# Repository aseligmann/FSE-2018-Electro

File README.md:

# FSE-2018-Electro
Repository for all software, schematics and designs made by the Electrical Department of Vermillion Racing for the 2018 season..

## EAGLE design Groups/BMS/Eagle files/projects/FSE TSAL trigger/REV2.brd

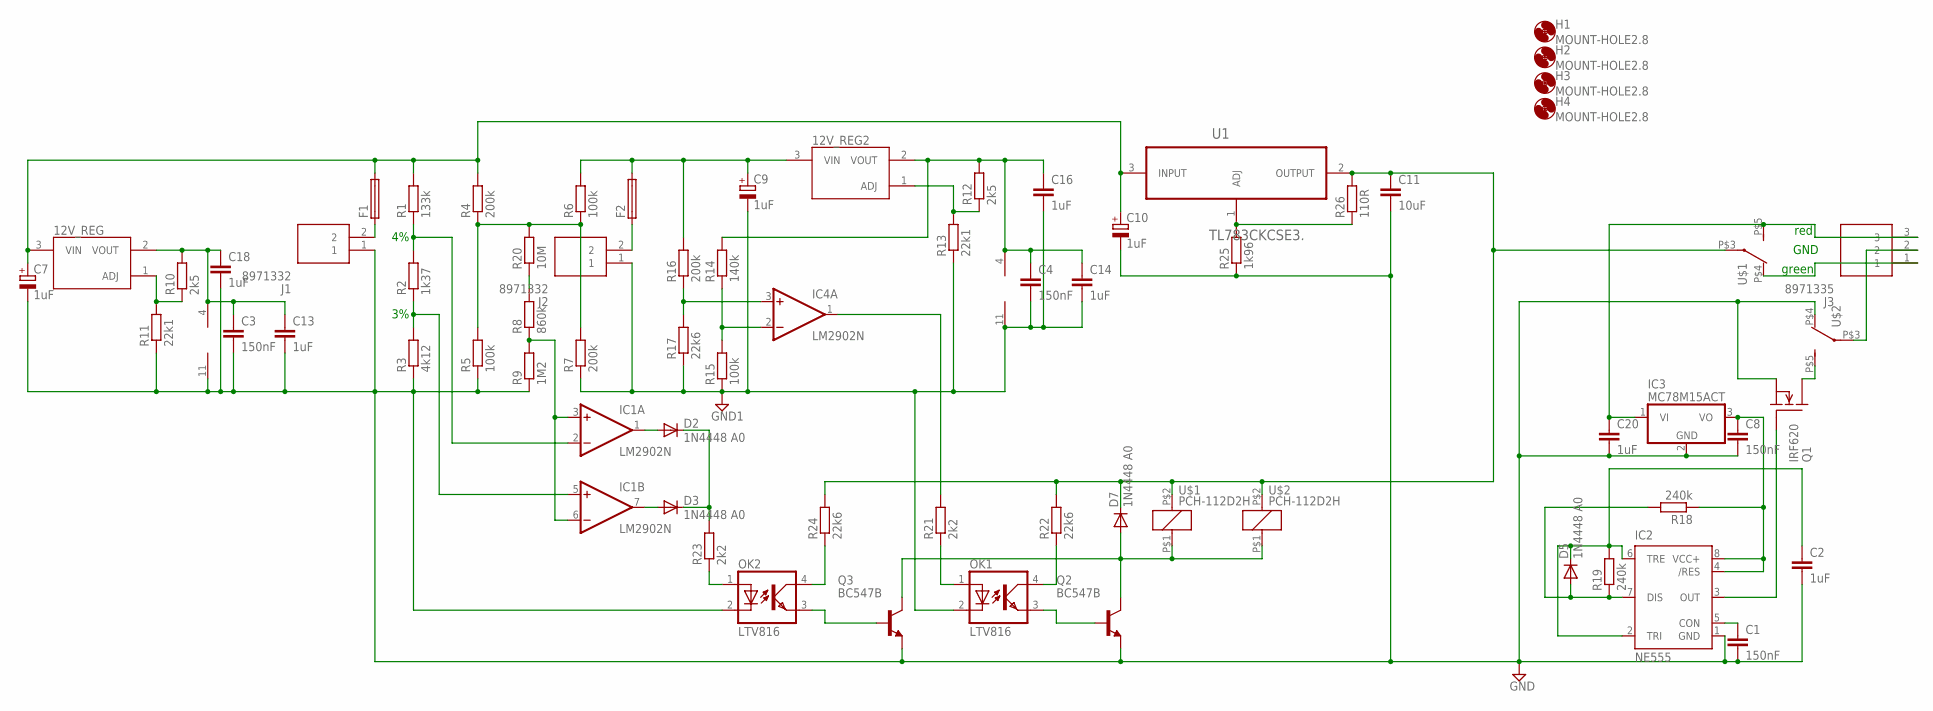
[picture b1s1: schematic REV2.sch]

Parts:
12V_REG, 12V_REG2: LR8LR8; TO92-LINE
C1, C3, C4, C8: 150nF; C050-024X044
C2, C13, C14, C16, C18, C20: 1uF; C025-030X050
C7, C9, C10: 1uF; E3,5-8
C11: 10uF; C050-075X075
D2, D3, D5, D7: 1N4448 A0; DO35-10
F1, F2: GSH15
H1, H2, H3, H4: MOUNT-HOLE2.8; 2,8
IC1, IC4: LM2902N; DIL14
IC2: NE555; DIL-08
IC3: MC78M15ACT; TO220V
J1, J2: 8971332; SHDR2W90P0X350_1X2_700X700X850
J3: 8971335; SHDR3W90P0X350_1X3_1050X700X85
OK1, OK2: LTV816; DIL04
Q1: IRF620; TO220
Q2, Q3: BC547B; TO92
R1: 133k; 0207/10
R2: 1k37; 0207/10
R3: 4k12; 0207/10
R4, R7, R16: 200k; 0207/10
R5, R6, R15: 100k; 0207/10
R8: 860k; 0207/10
R9: 1M2; 0207/10
R10, R12: 2k5; 0207/10
R11, R13: 22k1; 0207/10
R14: 140k; 0207/10
R17, R22, R24: 22k6; 0207/10
R18, R19: 240k; 0207/10
R20: 10M; 0207/10
R21, R23: 2k2; 0207/10
R25: 1k96; 0309/10
R26: 110R; 0309/10
U1: TL783CKCSE3.; TO254P457X1016X2222-3P
U$1, U$2: PCH-112D2H

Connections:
GND: C1.2, C2.2, C3.2, C7.-, C8.2, C10.-, C11.2, C13.2, C18.2, C20.2, IC1.11 (V-), IC2.1 (GND), IC3.2 (GND), J1.1, OK2.2 (C), Q1.3 (S), Q2.1 (E), Q3.1 (E), R3.1, R5.1, R9.1, R11.1, R25.1, U$2.P$4 (O)
GND1: C4.2, C9.-, C14.2, C16.2, IC4.11 (V-), J2.1, OK1.2 (C), R7.1, R13.1, R15.1, R17.1
unnamed: 12V_REG.3 (VIN), C7.+, C10.+, F1.2, R1.2, R4.2, U1.3 (INPUT)
unnamed: IC1.2 (-IN), R1.1, R2.2
unnamed: IC1.5 (+IN), R2.1, R3.2
unnamed: C11.1, D7.C, R22.2, R24.2, R26.2, U1.2 (OUTPUT), U$1.P$2 (1), U$1.P$3, U$2.P$2 (1)
unnamed: 12V_REG2.3 (VIN), C9.+, F2.2, R6.2, R16.2
unnamed: IC2.3 (OUT), Q1.1 (G)
unnamed: F1.1, J1.2
unnamed: IC4.1 (OUT), R21.2
unnamed: 12V_REG.2 (VOUT), C3.1, C13.1, C18.1, IC1.4 (V+), R10.2
unnamed: 12V_REG.1 (ADJ), R10.1, R11.2
unnamed: D2.A, IC1.1 (OUT)
unnamed: D3.A, IC1.7 (OUT)
unnamed: D2.C, D3.C, R23.2
unnamed: F2.1, J2.2
unnamed: C1.1, IC2.5 (CON)
unnamed: D5.A, IC2.7 (DIS), R18.2, R19.1
unnamed: C20.1, IC3.1 (VI), J3.3, U$1.P$5 (S)
unnamed: C2.1, D5.C, IC2.2 (TRI), IC2.6 (TRE), R19.2
unnamed: C8.1, IC2.4 (/RES), IC2.8 (VCC+), IC3.3 (VO), R18.1
unnamed: IC4.3 (+IN), R16.1, R17.2
unnamed: J3.1, U$1.P$4 (O)
unnamed: 12V_REG2.2 (VOUT), C4.1, C14.1, C16.1, IC4.4 (V+), R12.2, R14.2
unnamed: Q1.2 (D), U$2.P$5 (S)
unnamed: IC4.2 (-IN), R14.1, R15.2
unnamed: 12V_REG2.1 (ADJ), R12.1, R13.2
unnamed: R4.1, R5.2, R6.1, R7.2, R20.2
unnamed: IC1.3 (+IN), IC1.6 (-IN), R8.1, R9.2
unnamed: R8.2, R20.1
unnamed: R25.2, R26.1, U1.1 (ADJ)
unnamed: OK2.1 (A), R23.1
unnamed: OK2.4 (COL), R24.1
unnamed: J3.2, U$2.P$3
unnamed: D7.A, Q2.3 (C), Q3.3 (C), U$1.P$1 (2), U$2.P$1 (2)
unnamed: OK2.3 (EMIT), Q3.2 (B)
unnamed: OK1.1 (A), R21.1
unnamed: OK1.4 (COL), R22.1
unnamed: OK1.3 (EMIT), Q2.2 (B)

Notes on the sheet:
green
red
GND

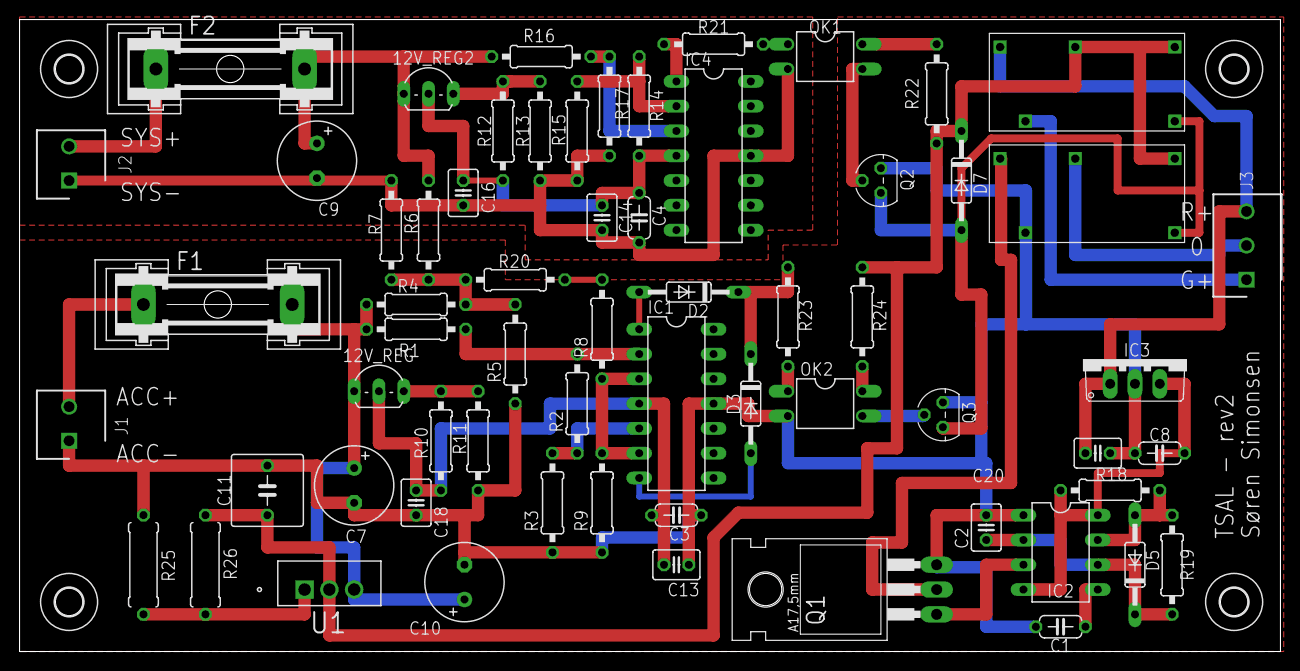
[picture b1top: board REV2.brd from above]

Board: 2 copper layers, 129.2 x 64.8 mm, 67 parts (0 on the bottom side), 39 nets.

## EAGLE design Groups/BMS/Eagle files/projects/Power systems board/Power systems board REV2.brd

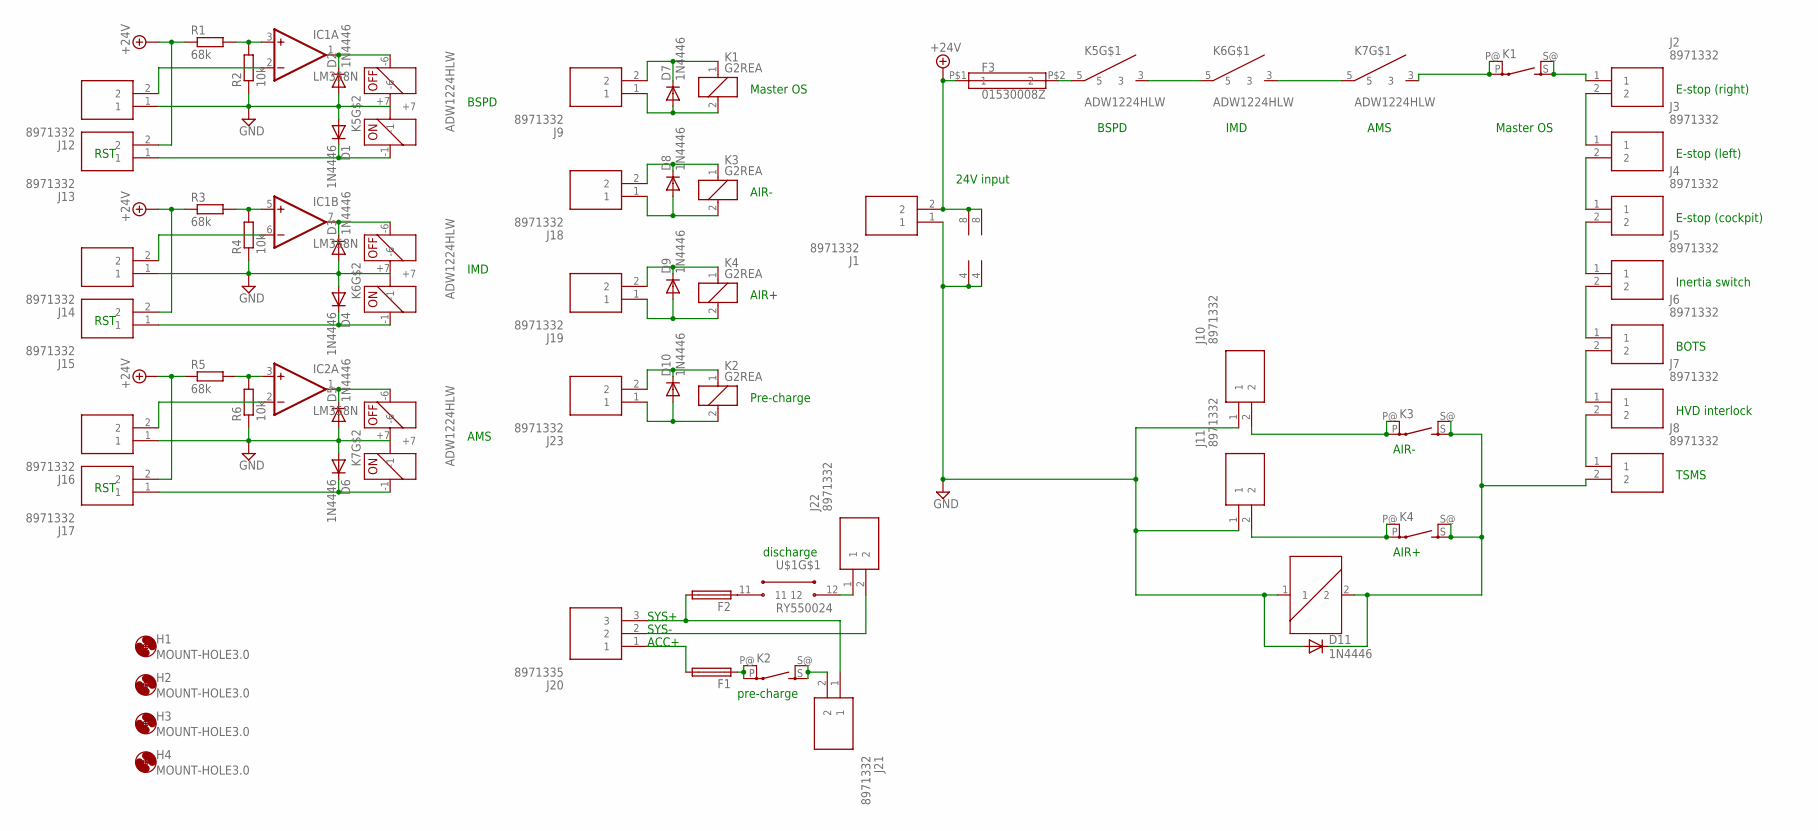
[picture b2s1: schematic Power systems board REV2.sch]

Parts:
D1, D2, D3, D4, D5, D6, D7, D8, D9, D10, D11: 1N4446; DO35-10
F1, F2: GSH15
F3: 01530008Z
H1, H2, H3, H4: MOUNT-HOLE3.0; 3,0
IC1, IC2: LM358N; DIL08
J1, J2, J3, J4, J5, J6, J7, J8, J9, J10, J11, J12, J13, J14, J15, J16, J17, J18, J19, J21, J22, J23: 8971332; SHDR2W90P0X350_1X2_700X700X850
J20: 8971335; SHDR3W90P0X350_1X3_1050X700X85
K1, K2, K3, K4: G2REA
K5, K6, K7: ADW1224HLW
R1, R3, R5: 68k; 0204/7
R2, R4, R6: 10k; 0204/7
U$1: RY550024

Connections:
+24V: F3.P$1 (1), IC1.8 (V+), IC2.8 (V+), J1.2, J13.2, J15.2, J17.2, R1.1, R3.1, R5.1
GND: D1.A, D2.A, D3.A, D4.A, D5.A, D6.A, D11.A, IC1.4 (V-), IC2.4 (V-), J1.1, J10.1, J11.1, J12.1, J14.1, J16.1, K5.+7, K6.+7, K7.+7, R2.1, R4.1, R6.1, U$1.1
unnamed: IC1.3 (+IN), R1.2, R2.2
unnamed: K5.3, K6.5
unnamed: K6.3, K7.5
unnamed: K1.P, K1.P@, K7.3
unnamed: J2.1, K1.S, K1.S@ (S)
unnamed: J2.2, J3.1
unnamed: J3.2, J4.1
unnamed: J4.2, J5.1
unnamed: J5.2, J6.1
unnamed: J6.2, J7.1
unnamed: J7.2, J8.1
unnamed: D11.C, J8.2, K3.S, K3.S@ (S), K4.S, K4.S@ (S), U$1.2
unnamed: J10.2, K3.P, K3.P@
unnamed: J11.2, K4.P, K4.P@
unnamed: F1.1, K2.P, K2.P@
unnamed: D2.C, IC1.1 (OUT), K5.-6
unnamed: IC1.2 (-IN), J12.2
unnamed: D1.C, J13.1, K5.-1
unnamed: IC1.5 (+IN), R3.2, R4.2
unnamed: IC1.6 (-IN), J14.2
unnamed: D5.C, IC2.1 (OUT), K7.-6
unnamed: D4.C, J15.1, K6.-1
unnamed: D3.C, IC1.7 (OUT), K6.-6
unnamed: D7.C, J9.2, K1.1
unnamed: IC2.2 (-IN), J16.2
unnamed: IC2.3 (+IN), R5.2, R6.2
unnamed: D7.A, J9.1, K1.2
unnamed: D6.C, J17.1, K7.-1
unnamed: D8.C, J18.2, K3.1
unnamed: D8.A, J18.1, K3.2
unnamed: D9.C, J19.2, K4.1
unnamed: D9.A, J19.1, K4.2
unnamed: F1.2, J20.1
unnamed: F2.2, J20.3, J21.1
unnamed: J21.2, K2.S, K2.S@ (S)
unnamed: J20.2, J22.2
unnamed: D10.C, J23.2, K2.1
unnamed: D10.A, J23.1, K2.2
unnamed: F3.P$2 (2), K5.5
unnamed: F2.1, U$1.11
unnamed: J22.1, U$1.12

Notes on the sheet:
24V input
BSPD
IMD
AMS
Master OS
E-stop (right)
E-stop (left)
E-stop (cockpit)
Inertia switch
BOTS
HVD interlock
TSMS
Pre-charge
AIR-
AIR+
RST
SYS+
SYS-
ACC+
pre-charge
discharge

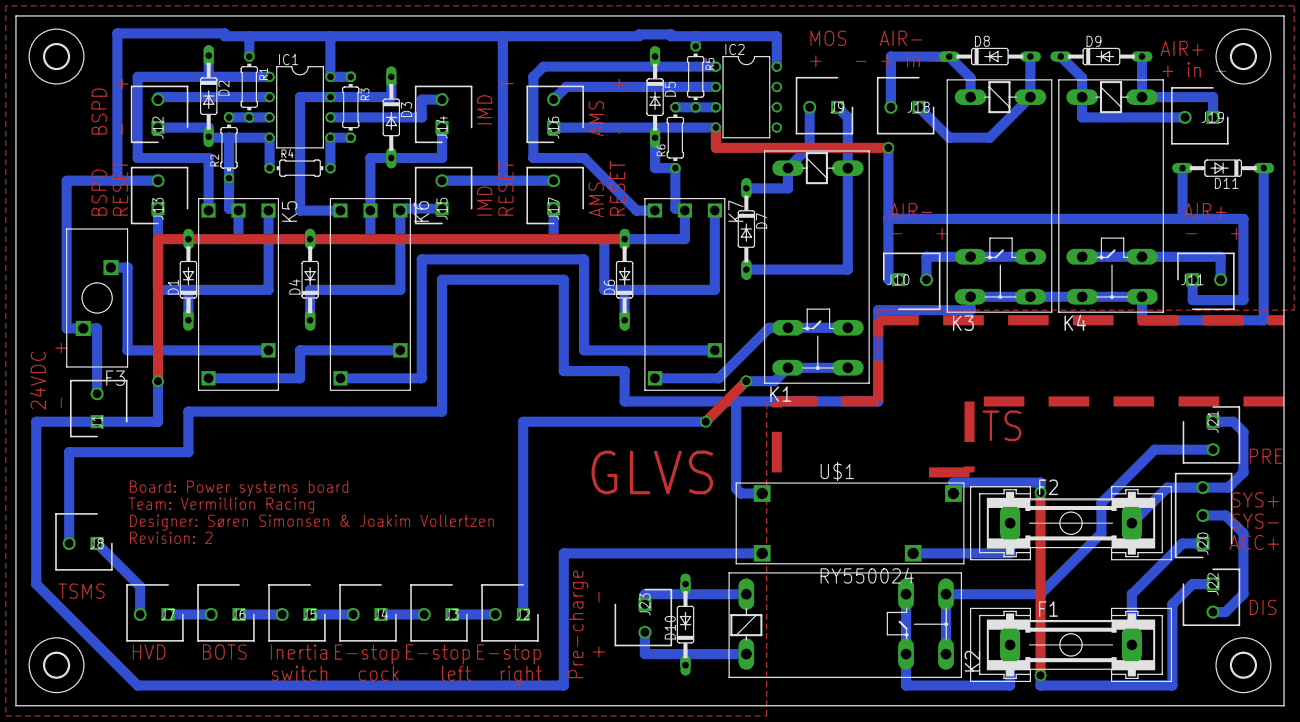
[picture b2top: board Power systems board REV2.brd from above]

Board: 2 copper layers, 158.8 x 86.4 mm, 57 parts (0 on the bottom side), 43 nets.

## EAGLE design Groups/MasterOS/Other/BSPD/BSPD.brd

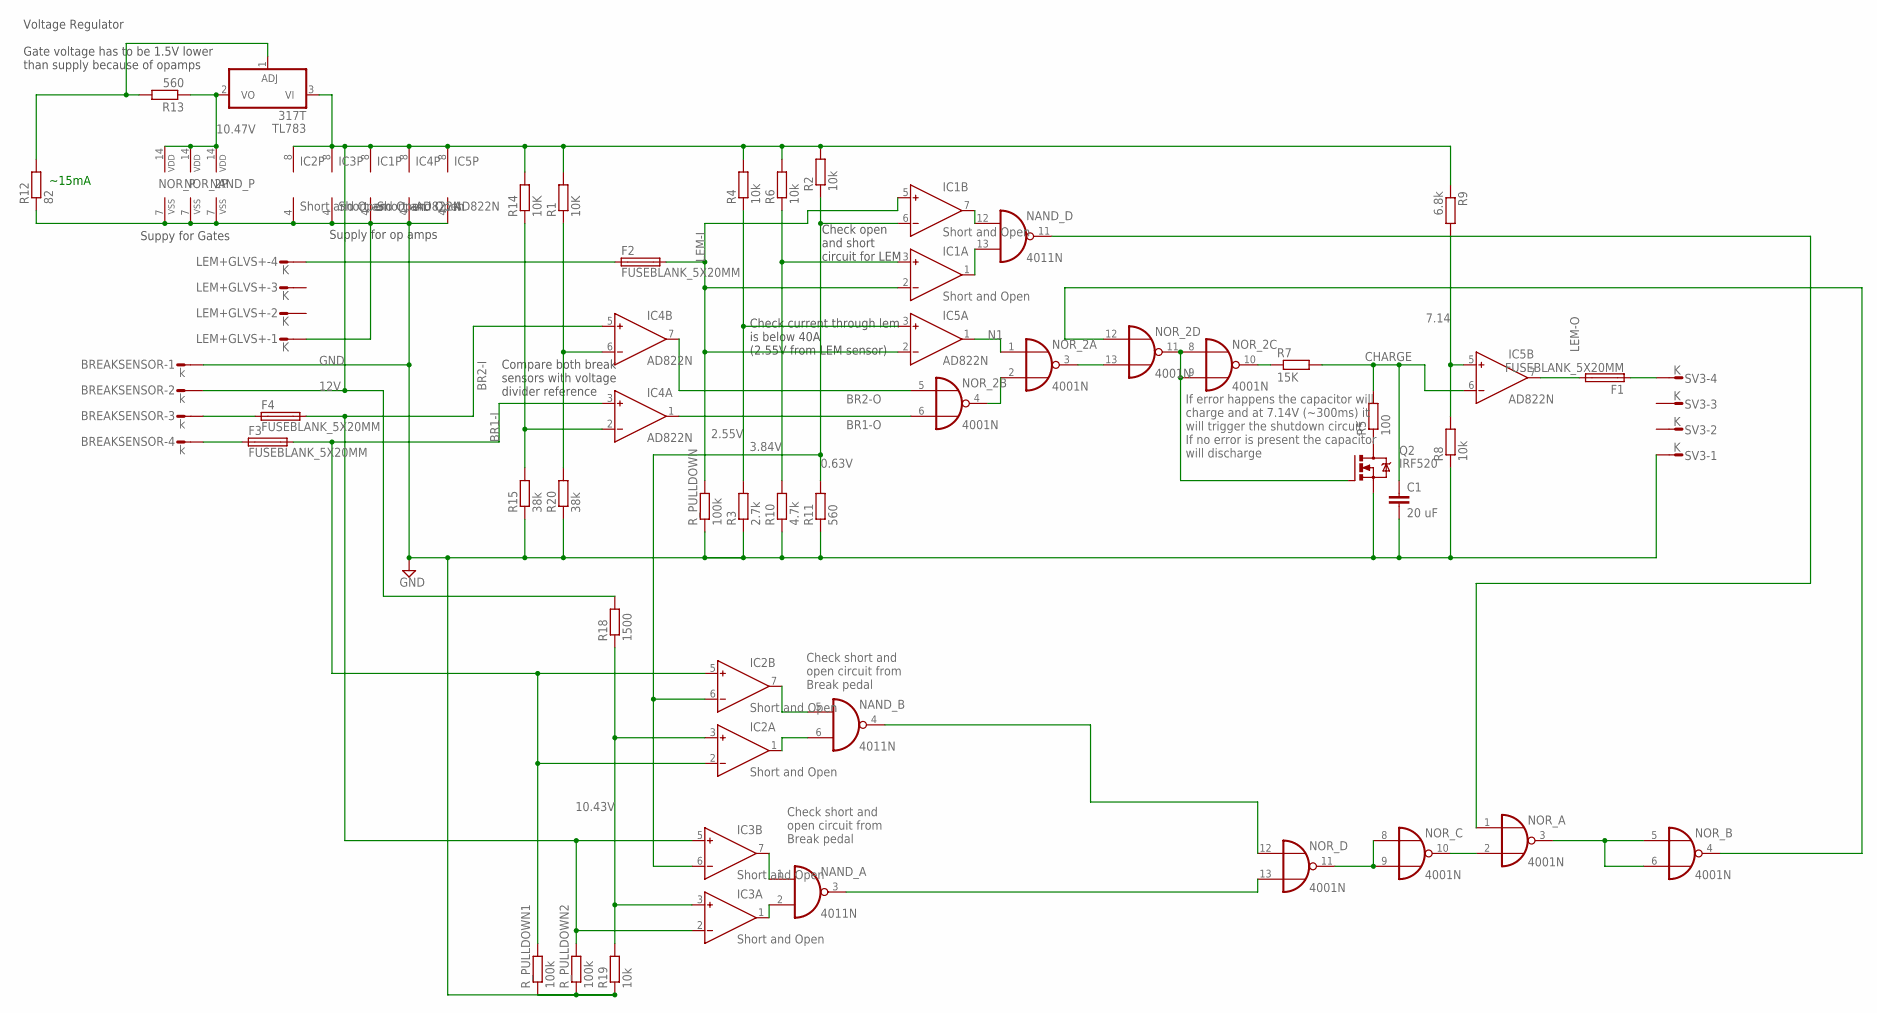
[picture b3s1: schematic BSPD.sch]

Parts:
BREAKSENSOR: k; L04P
C1: 20 uF; C2.5-5
F1, F2, F3, F4: FUSEBLANK_5X20MM; FUSE_HOLDER_5X20MM
IC1, IC2, IC3: Short and Open; DIL08
IC4, IC5: AD822N; DIL08
LEM+GLVS+: K; L04P
NAND_: 4011N; DIL14
NOR_, NOR_2: 4001N; DIL14
Q2: IRF520; TO220BV
R1, R14: 10K; 0204/7
R2, R4, R6, R8: 10k; 0204/7
R3: 2.7k; 0204/7
R5: 100; 0207/10
R7: 15K; 0207/10
R9: 6.8k; 0204/7
R10: 4.7k; 0204/7
R11, R13: 560; 0204/7
R12: 82; 0204/7
R15, R20: 38k; 0207/10
R18: 1500; 0207/10
R19: 10k; 0207/10
R_PULLDOWN, R_PULLDOWN1, R_PULLDOWN2: 100k; 0204/7
SV3: K; L04P
TL783: 317T; TO220H

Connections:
0.63V: IC1.6 (IN-), IC2.6 (IN-), IC3.6 (IN-), R2.1, R11.2
2.55V: IC5.3 (IN+), R3.2, R4.1
3.84V: IC1.3 (IN+), R6.1, R10.2
7.14: IC5.5 (IN+), R8.2, R9.2
10.43V: IC2.3 (IN+), IC3.3 (IN+), R18.1, R19.2
10.47V: NAND_.14 (VDD), NOR_.14 (VDD), NOR_2.14 (VDD), R13.1, TL783.2 (VO)
12V: BREAKSENSOR.2, IC1.8 (V+), IC2.8 (V+), IC3.8 (V+), IC4.8 (V+), IC5.8 (V+), R1.2, R2.2, R4.2, R6.2, R9.1, R14.2, R18.2, TL783.3 (VI)
BR1-I: F3.2, IC2.2 (IN-), IC2.5 (IN+), IC4.3 (IN+), R_PULLDOWN1.2
BR1-O: IC4.1 (OUT), NOR_2.6 (I1)
BR2-I: F4.2, IC3.2 (IN-), IC3.5 (IN+), IC4.5 (IN+), R_PULLDOWN2.2
BR2-O: IC4.7 (OUT), NOR_2.5 (I0)
CHARGE: C1.1, IC5.6 (IN-), R5.2, R7.2
GND: BREAKSENSOR.1, C1.2, IC1.4 (V-), IC2.4 (V-), IC3.4 (V-), IC4.4 (V-), IC5.4 (V-), LEM+GLVS+.1, NAND_.7 (VSS), NOR_.7 (VSS), NOR_2.7 (VSS), Q2.S, R3.1, R8.1, R10.1, R11.1, R12.1, R15.1, R19.1, R20.1, R_PULLDOWN.1, R_PULLDOWN1.1, R_PULLDOWN2.1, SV3.1
LEM-I: F2.2, IC1.2 (IN-), IC1.5 (IN+), IC5.2 (IN-), R_PULLDOWN.2
LEM-O: F1.2, IC5.7 (OUT)
N1: IC5.1 (OUT), NOR_2.1 (I0)
unnamed: NOR_2.3 (O), NOR_2.13 (I1)
unnamed: IC4.2 (IN-), R14.1, R15.2
unnamed: NOR_2.2 (I1), NOR_2.4 (O)
unnamed: R12.2, R13.2, TL783.1 (ADJ)
unnamed: NOR_2.8 (I0), NOR_2.9 (I1), NOR_2.11 (O), Q2.G
unnamed: NOR_.8 (I0), NOR_.9 (I1), NOR_.11 (O)
unnamed: NAND_.3 (O), NOR_.13 (I1)
unnamed: NOR_.4 (O), NOR_2.12 (I0)
unnamed: NOR_.2 (I1), NOR_.10 (O)
unnamed: IC1.1 (OUT), NAND_.13 (I1)
unnamed: Q2.D, R5.1
unnamed: F1.1, SV3.4
unnamed: F2.1, LEM+GLVS+.4
unnamed: IC1.7 (OUT), NAND_.12 (I0)
unnamed: NAND_.4 (O), NOR_.12 (I0)
unnamed: IC2.1 (OUT), NAND_.6 (I1)
unnamed: IC2.7 (OUT), NAND_.5 (I0)
unnamed: IC3.1 (OUT), NAND_.2 (I1)
unnamed: IC3.7 (OUT), NAND_.1 (I0)
unnamed: NAND_.11 (O), NOR_.1 (I0)
unnamed: BREAKSENSOR.4, F3.1
unnamed: NOR_.3 (O), NOR_.5 (I0), NOR_.6 (I1)
unnamed: NOR_2.10 (O), R7.1
unnamed: BREAKSENSOR.3, F4.1
NS$3: IC4.6 (IN-), R1.1, R20.2

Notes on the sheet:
~15mA
Voltage Regulator Gate voltage has to be 1.5V lower than supply because of opamps
Suppy for Gates
Supply for op amps
Compare both break sensors with voltage divider reference
Check open and short circuit for LEM
Check current through lem is below 40A (2.55V from LEM sensor)
Check short and open circuit from Break pedal
If error happens the capacitor will charge and at 7.14V (~300ms) it will trigger the shutdown circuit If no error is present the capacitor will discharge

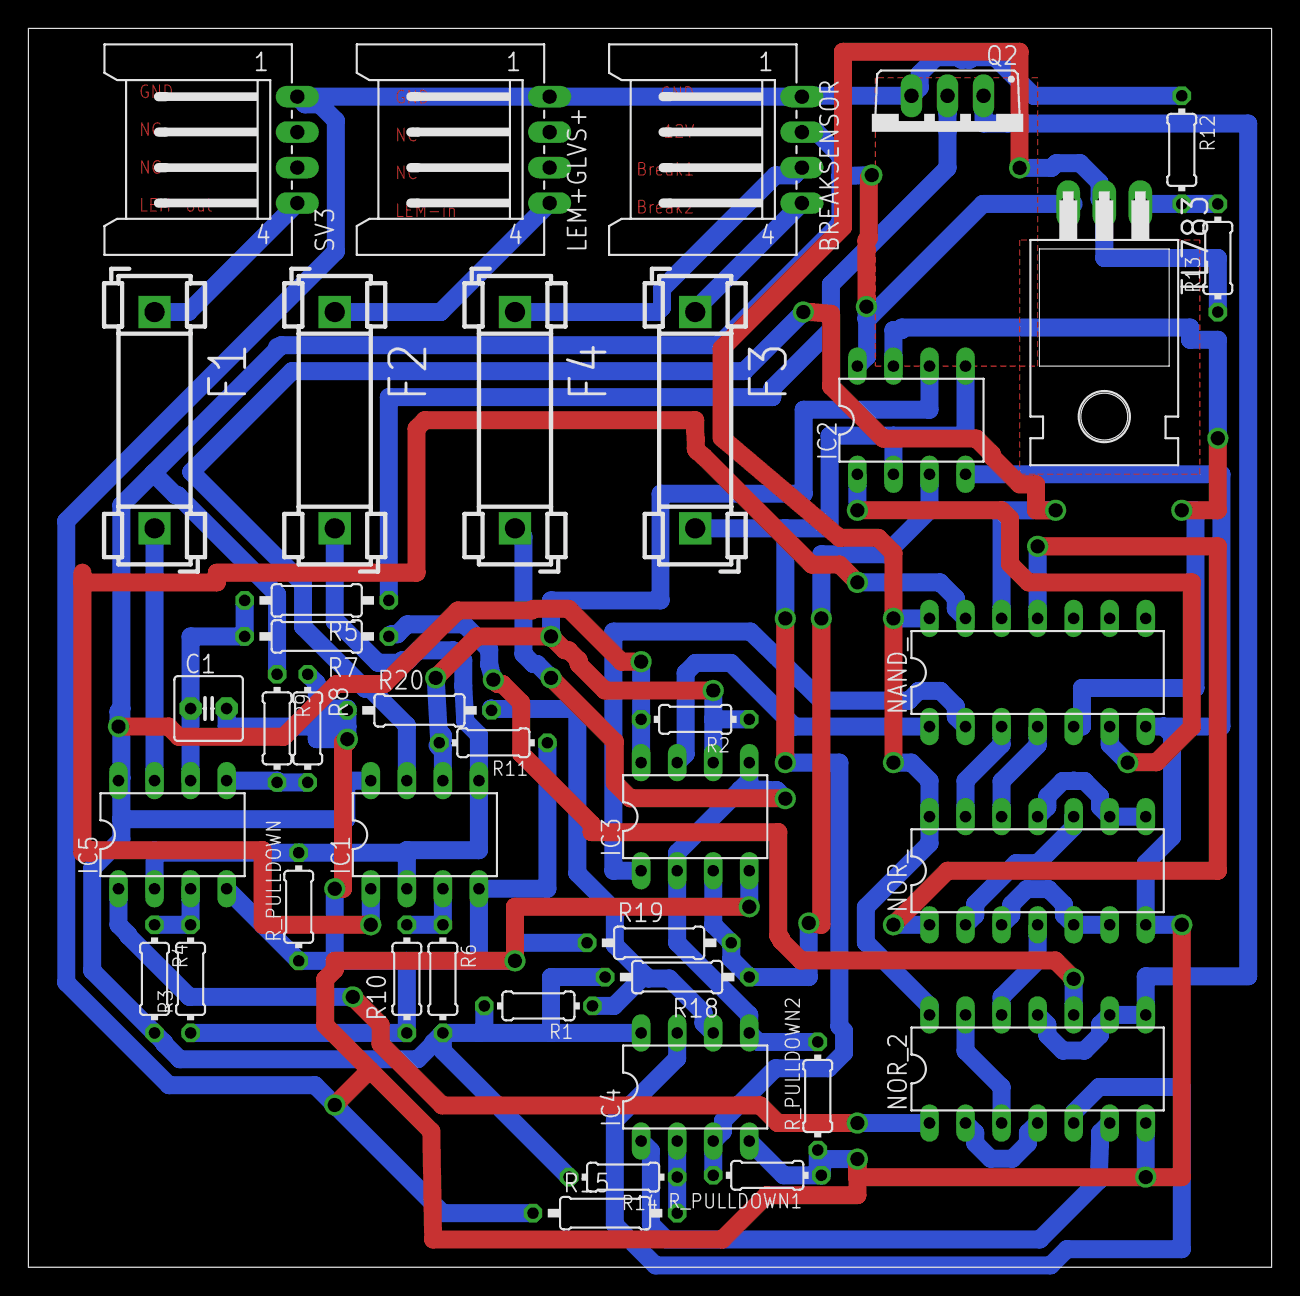
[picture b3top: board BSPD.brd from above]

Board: 2 copper layers, 87.6 x 87.3 mm, 39 parts (0 on the bottom side), 41 nets.

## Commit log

2018-06-21 Initial commit to establish folder structure
2018-06-21 Added group folders
2018-06-21 Added gitignore
2018-06-21 Remove DS_Store
2018-08-07 Documentation collected
2018-08-29 Added Torque Vectoring work done in LabView, done by Dominik.
